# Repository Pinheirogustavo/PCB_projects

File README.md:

# PCB Projects

## Conexões presentes nas barras de pinos

### Barra de "tensoes"

- Earth: Terra virtual implementado com LM675
- VCC: +(MaxTensao da fonte utilizada / 2) Tensao NÃO regulada
- VEE:-(MaxTensao da fonte utilizada / 2)  Tensao NÃO regulada
- +9V: regulador 7809
- -9V: regulador 7909
- +5V: regulador 7805
- -5V: regulador 7905
- +3.3V: regulador 1117T-3.3

### Barra "Sinais analogicos"
- I1: corrente 1 dada pela fonte Howland
- I2: corrente 2 dada pela fonte Howland (caso bipolar)
- Ampl1: Tensão de saída condicionada do INA que monitora a corrente I1
- Ampl2: Tensão de saída condicionada do INA que monitora a corrente I2
- Sin1: Sinal alternado 1 gerado por AD9833/9850. Sem amplificação
- Sin2: Sinal alternado 2 gerado por AD9833/9850. Sem amplificação
- SinA: Sinal alternado 1 com controle de amplitude (talvez freq e fase)
- SinB: Sinal alternado 2 com controle de amplitude (talvez freq e fase)

### Barra "comunicacao"
- SINC: Sinal de sincronismo (ainda a definir)
- SDA(1-3)/SCL(1-3): Três pares de pinos reservados para comunicação - I2C
- SPI_COPI: comunicação SPI Controller Out Peripheral In
- SPI_CIPO: comunicação SPI Controller In, Peripheral Out
- SPI_clk: pino de clock que estabelece o sincronismo da comunicação SPI
- CS(x): pinos para selecionar o chip desejado (Chip Select)
> CS (AD9833): seleciona o gerador de sinais AD9833

> CS (X9c10x): seleciona o potenciometro digital do circuito de controle da corrente

###### comunicação I2C

SDA1/SCL1: implementado nos módulos "Gerador de sinais", com resistores pullup (Rp) para dispositivos de 3.3V;

SDA2/SCL2: implementado nos módulos "Fonte de corrente", com resistores pullup (Rp) para dispositivos de 5.0V. 

I2C arduino: https://docs.arduino.cc/learn/communication/wire

SPI arduino https://docs.arduino.cc/learn/communication/spi?_gl=1*1

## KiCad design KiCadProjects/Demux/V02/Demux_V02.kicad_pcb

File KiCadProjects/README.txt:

Versao do CAD: KiCad 7.0

------------------------------------------------------------------------------------------------------------------------------------------
Como adicionar bibliotecas

- Bibliotecas prontas da internet (salvar em Projeto Global): https://forum.digikey.com/t/importing-the-digi-key-kicad-library-into-kicad-5-0-0/4075
	caminho:/PCB_projects/KiCadProjects/libraries/

- Bibliotecas criadas pelo autor:  Usar o editor de simbolos e de footprint do kicad, salvar em Projeto Global
	caminho:/PCB_projects/KiCadProjects/libraries/MyCreates
------------------------------------------------------------------------------------------------------------------------------------------

Placa 90x100mm face simples

Trilhas azuis: trilhas dispostas na face de cobre inferior

Trilhas vermelhas: Representam jumpers, estao dispostas na face de cobre superior

------------------------------------------------------------------------------------------------------------------------------------------

Regras de layout PCB

- largura da trilha = 50 mils (1,27 mm)
 	O valor mínimo é de 8 mils, mas isso gera uma trilha extremamente fina
- Espaçamento entre trilhas = 50 mils (1,27 mm)
	O grid deve ser maior que o diâmetro da fresa utilizada (>0,2mm)
- Definir o algoritmo de auto-roteamento no CAD como “Grid Router” (precisa adicionar plugin)
- Definir o diâmetro do contorno em 0,5mm

------------------------------------------------------------------------------------------------------------------------------------------

Orientações para layout PCB

- Criar trilhas de alimentação, de terra e de clock.
- Fazer as trilhas de alimentação com largura maior
- Evitar trilhas muito longas
- Preferir mudanças de direção de 45º nas trilhas
- Evitar que trilhas de sinais críticos (clock e altas freqüências) fiquem paralelas por muito tempo
- Evitar ligações diretas entre as entradas de alimentação de Cis
- Colocar um LED indicando que a placa está energizada
-Colocar pontos de acesso para medir com o osciloscópio
- Usar soquetes para os CIs

------------------------------------------------------------------------------------------------------------------------------------------
Alguns footprints de componentes comuns e suas melhores  escolhas (ou até achar algo melhor)

Resistores -  11779 Resistor_THT:R_Axial_DIN0207_L6.3mm_D2.5mm_P7.62mm_Horizontal
Capacitores eletrolíticos - 525 Capacitor_THT:CP_Radial_D5.0mm_P2.50mm
Diodos -  7485 Diode_THT:D_DO-41_SOD81_P10.16mm_Horizontal
LED - 8642 LED_THT:LED_D5.0mm
conectores fêmea -  5813/6090 Connector_PinSocket_2.54mm:PinSocket_1xXX_P2.54mm_Vertical
conectores macho -  4855/5132 Connector_PinHeader_2.54mm:PinHeader_1xXX_P2.54mm_Vertical 
conector p4 de bateria - 1150 Connector_BarrelJack:BarrelJack_GCT_DCJ200-10-A_Horizontal

------------------------------------------------------------------------------------------------------------------------------------------
Tamanho de pad de componentes comuns e suas melhores  escolhas (ou até achar algo melhor). O tamanho do furo (0,8mm) não precisa ser configurado agora pois pode ser modificado na hora da produção (FlatCAM).

Resistores -  circular 2,5mm 
Capacitores eletrolíticos -  	+ circular 2mm	-retangular2x2,5mm
Diodos -   circular 2,5mm 
LED - 	+ circular 2mm	-retangular2x2,5mm
Barra de pinos - circular 2mm
conector p4 de bateria - oval3x4,2mm retangular4,6x3mm

------------------------------------------------------------------------------------------------------------------------------------------
FONTE DE TENSAO

v01;v02 SW1: Botão DPDT com trava para ligar e desligar a fonte. https://www.multcomercial.com.br/chave-push-button-7x7-com-trava.html
v03;v04 Chave gangorra kcd1 para ligar e desligar a fonte.

Os reguladores estao localizados na borda da placa, alinhados e igualmente espaçados, sendo possivel utilizar único dissipador

Segundo icone, ao lado do simbolo de disquete. Para editar as regras de furos, tamanhos de trilhas... sempre conferir. 

Icone de lista. Verifica as regras.

------------------------------------------------------------------------------------------------------------------------------------------

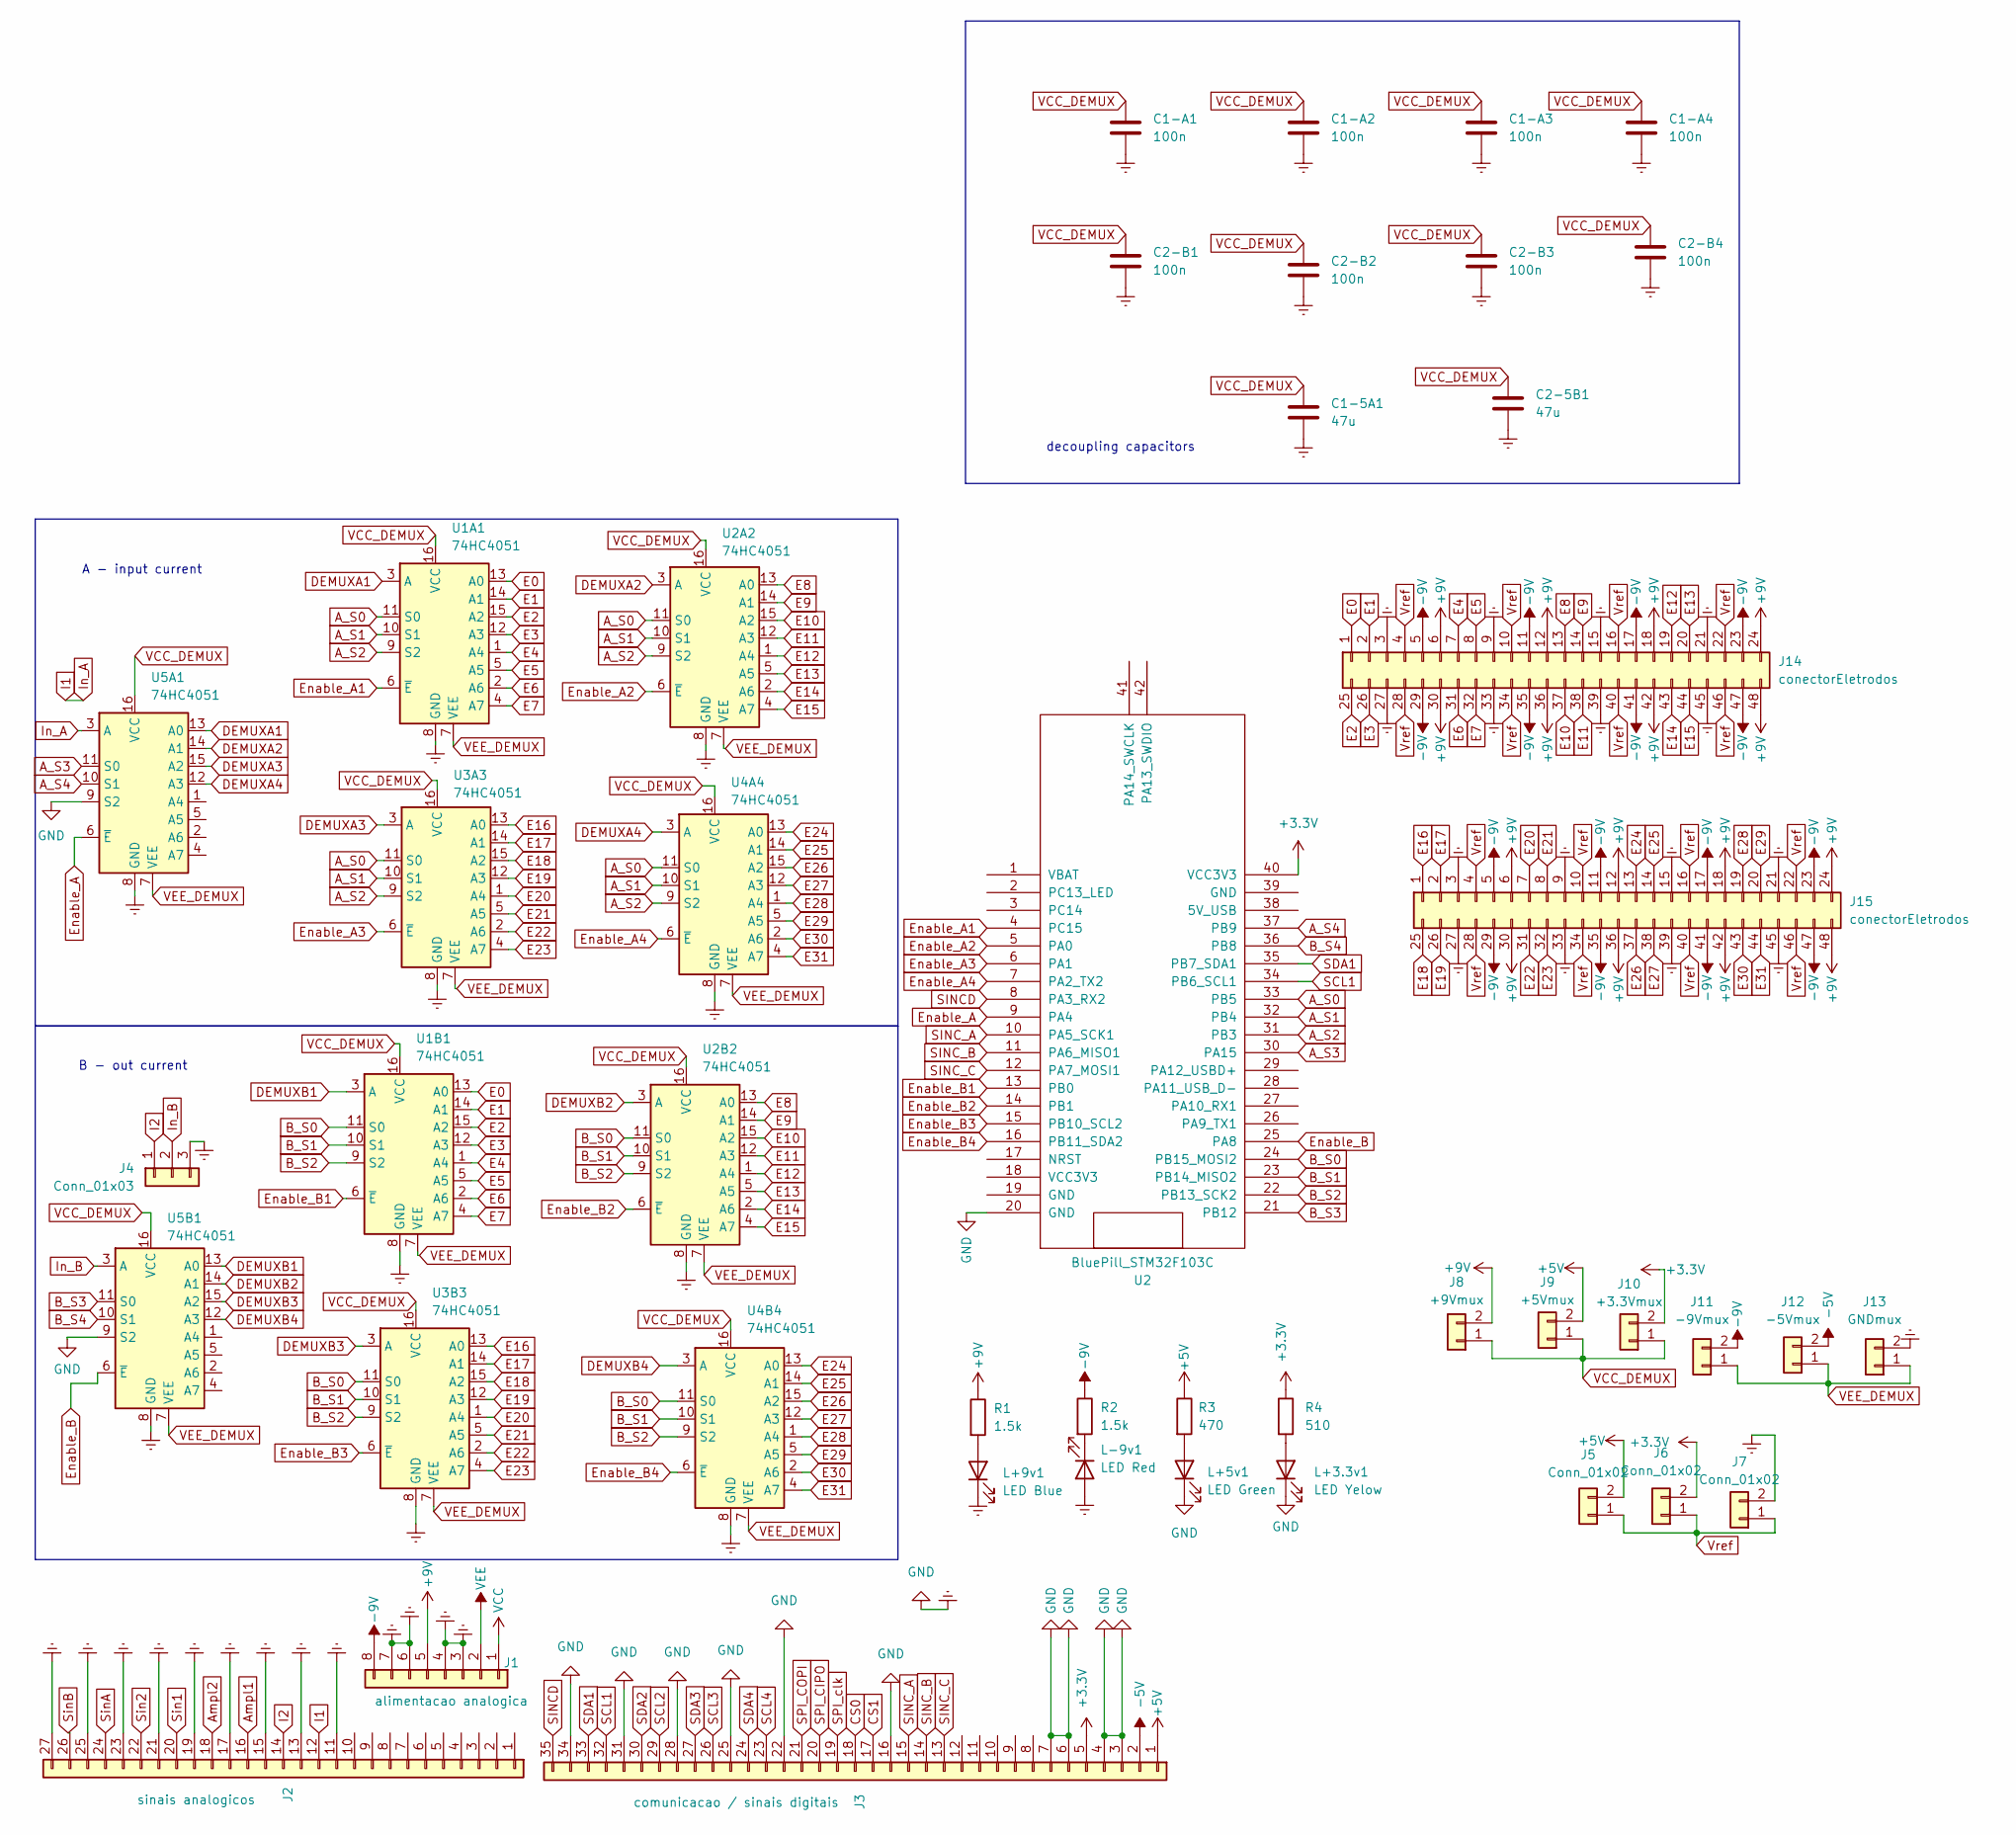
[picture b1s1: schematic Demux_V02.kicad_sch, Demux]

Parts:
C1-5A1, C2-5B1: 47u; CP_Radial_D5.0mm_P2.50mm
C1-A1, C1-A2, C1-A3, C1-A4, C2-B1, C2-B2, C2-B3, C2-B4: 100n; C_Disc_D3.0mm_W1.6mm_P2.50mm
J1: alimentacao analogica; PinHeader_1x08_P2.54mm_Vertical
J2: sinais analogicos; PinHeader_1x27_P2.54mm_Vertical
J3: comunicacao / sinais digitais; PinHeader_1x35_P2.54mm_Vertical
J4: Conn_01x03; PinHeader_1x03_P2.54mm_Vertical
J5, J6, J7: Conn_01x02; PinHeader_1x02_P2.54mm_Vertical
J8: +9Vmux; PinHeader_1x02_P2.54mm_Vertical
J9: +5Vmux; PinHeader_1x02_P2.54mm_Vertical
J10: +3.3Vmux; PinHeader_1x02_P2.54mm_Vertical
J11: -9Vmux; PinHeader_1x02_P2.54mm_Vertical
J12: -5Vmux; PinHeader_1x02_P2.54mm_Vertical
J13: GNDmux; PinHeader_1x02_P2.54mm_Vertical
J14, J15: conectorEletrodos; PinHeader_2x24_P2.54mm_Vertical
L+3.3v1: LED Yelow; LED_D5.0mm
L+5v1: LED Green; LED_D5.0mm
L+9v1: LED Blue; LED_D5.0mm
L-9v1: LED Red; LED_D5.0mm
R1, R2: 1.5k; R_Axial_DIN0207_L6.3mm_D2.5mm_P7.62mm_Horizontal
R3: 470; R_Axial_DIN0207_L6.3mm_D2.5mm_P7.62mm_Horizontal
R4: 510; R_Axial_DIN0207_L6.3mm_D2.5mm_P7.62mm_Horizontal
U1A1, U1B1, U2A2, U2B2, U3A3, U3B3, U4A4, U4B4, U5A1, U5B1: 74HC4051; N16
U2: BluePill_STM32F103C

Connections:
+3.3V: J3.5, J6.2, J10.2, R4.1, U2.40 (VCC3V3)
+5V: J3.1, J5.2, J9.2, R3.1
+9V: J1.5, J8.2, J14.6, J14.12, J14.18, J14.24, J14.30, J14.36, J14.42, J14.48, J15.6, J15.12, J15.18, J15.24, J15.30, J15.36, J15.42, J15.48, R1.1
-5V: J3.2, J12.2
-9V: J1.8, J11.2, J14.5, J14.11, J14.17, J14.23, J14.29, J14.35, J14.41, J14.47, J15.5, J15.11, J15.17, J15.23, J15.29, J15.35, J15.41, J15.47, R2.1
A_S0: U1A1.11 (S0), U2.33 (PB5), U2A2.11 (S0), U3A3.11 (S0), U4A4.11 (S0)
A_S1: U1A1.10 (S1), U2.32 (PB4), U2A2.10 (S1), U3A3.10 (S1), U4A4.10 (S1)
A_S2: U1A1.9 (S2), U2.31 (PB3), U2A2.9 (S2), U3A3.9 (S2), U4A4.9 (S2)
A_S3: U2.30 (PA15), U5A1.11 (S0)
A_S4: U2.37 (PB9), U5A1.10 (S1)
Ampl1: J2.16
Ampl2: J2.18
B_S0: U1B1.11 (S0), U2.24 (PB15_MOSI2), U2B2.11 (S0), U3B3.11 (S0), U4B4.11 (S0)
B_S1: U1B1.10 (S1), U2.23 (PB14_MISO2), U2B2.10 (S1), U3B3.10 (S1), U4B4.10 (S1)
B_S2: U1B1.9 (S2), U2.22 (PB13_SCK2), U2B2.9 (S2), U3B3.9 (S2), U4B4.9 (S2)
B_S3: U2.21 (PB12), U5B1.11 (S0)
B_S4: U2.36 (PB8), U5B1.10 (S1)
CS0: J3.18
CS1: J3.17
DEMUXA1: U1A1.3 (A), U5A1.13 (A0)
DEMUXA2: U2A2.3 (A), U5A1.14 (A1)
DEMUXA3: U3A3.3 (A), U5A1.15 (A2)
DEMUXA4: U4A4.3 (A), U5A1.12 (A3)
DEMUXB1: U1B1.3 (A), U5B1.13 (A0)
DEMUXB2: U2B2.3 (A), U5B1.14 (A1)
DEMUXB3: U3B3.3 (A), U5B1.15 (A2)
DEMUXB4: U4B4.3 (A), U5B1.12 (A3)
E0: J14.1, U1A1.13 (A0), U1B1.13 (A0)
E1: J14.2, U1A1.14 (A1), U1B1.14 (A1)
E2: J14.25, U1A1.15 (A2), U1B1.15 (A2)
E3: J14.26, U1A1.12 (A3), U1B1.12 (A3)
E4: J14.7, U1A1.1 (A4), U1B1.1 (A4)
E5: J14.8, U1A1.5 (A5), U1B1.5 (A5)
E6: J14.31, U1A1.2 (A6), U1B1.2 (A6)
E7: J14.32, U1A1.4 (A7), U1B1.4 (A7)
E8: J14.13, U2A2.13 (A0), U2B2.13 (A0)
E9: J14.14, U2A2.14 (A1), U2B2.14 (A1)
E10: J14.37, U2A2.15 (A2), U2B2.15 (A2)
E11: J14.38, U2A2.12 (A3), U2B2.12 (A3)
E12: J14.19, U2A2.1 (A4), U2B2.1 (A4)
E13: J14.20, U2A2.5 (A5), U2B2.5 (A5)
E14: J14.43, U2A2.2 (A6), U2B2.2 (A6)
E15: J14.44, U2A2.4 (A7), U2B2.4 (A7)
E16: J15.1, U3A3.13 (A0), U3B3.13 (A0)
E17: J15.2, U3A3.14 (A1), U3B3.14 (A1)
E18: J15.25, U3A3.15 (A2), U3B3.15 (A2)
E19: J15.26, U3A3.12 (A3), U3B3.12 (A3)
E20: J15.7, U3A3.1 (A4), U3B3.1 (A4)
E21: J15.8, U3A3.5 (A5), U3B3.5 (A5)
E22: J15.31, U3A3.2 (A6), U3B3.2 (A6)
E23: J15.32, U3A3.4 (A7), U3B3.4 (A7)
E24: J15.13, U4A4.13 (A0), U4B4.13 (A0)
E25: J15.14, U4A4.14 (A1), U4B4.14 (A1)
E26: J15.37, U4A4.15 (A2), U4B4.15 (A2)
E27: J15.38, U4A4.12 (A3), U4B4.12 (A3)
E28: J15.19, U4A4.1 (A4), U4B4.1 (A4)
E29: J15.20, U4A4.5 (A5), U4B4.5 (A5)
E30: J15.43, U4A4.2 (A6), U4B4.2 (A6)
E31: J15.44, U4A4.4 (A7), U4B4.4 (A7)
Earth: C1-5A1.2, C1-A1.2, C1-A2.2, C1-A3.2, C1-A4.2, C2-5B1.2, C2-B1.2, C2-B2.2, C2-B3.2, C2-B4.2, J1.3, J1.4, J1.6, J1.7, J2.11, J2.13, J2.15, J2.17, J2.19, J2.21, J2.23, J2.25, J2.27, J3.3, J3.4, J3.6, J3.7, J3.16, J3.22, J3.25, J3.28, J3.31, J3.34, J4.3, J7.2, J13.2, J14.3, J14.9, J14.15, J14.21, J14.27, J14.33, J14.39, J14.45, J15.3, J15.9, J15.15, J15.21, J15.27, J15.33, J15.39, J15.45, L+3.3v1.1 (K), L+5v1.1 (K), L+9v1.1 (K), L-9v1.2 (A), U1A1.8 (GND), U1B1.8 (GND), U2.20 (GND), U2A2.8 (GND), U2B2.8 (GND), U3A3.8 (GND), U3B3.8 (GND), U4A4.8 (GND), U4B4.8 (GND), U5A1.8 (GND), U5A1.9 (S2), U5B1.8 (GND), U5B1.9 (S2)
Enable_A: U2.9 (PA4), U5A1.6 (~E)
Enable_A1: U1A1.6 (~E), U2.4 (PC15)
Enable_A2: U2.5 (PA0), U2A2.6 (~E)
Enable_A3: U2.6 (PA1), U3A3.6 (~E)
Enable_A4: U2.7 (PA2_TX2), U4A4.6 (~E)
Enable_B: U2.25 (PA8), U5B1.6 (~E)
Enable_B1: U1B1.6 (~E), U2.13 (PB0)
Enable_B2: U2.14 (PB1), U2B2.6 (~E)
Enable_B3: U2.15 (PB10_SCL2), U3B3.6 (~E)
Enable_B4: U2.16 (PB11_SDA2), U4B4.6 (~E)
I1: J2.12, U5A1.3 (A)
I2: J2.14, J4.1
In_B: J4.2, U5B1.3 (A)
unnamed: L+3.3v1.2 (A), R4.2
unnamed: L+5v1.2 (A), R3.2
unnamed: L+9v1.2 (A), R1.2
unnamed: L-9v1.1 (K), R2.2
SCL1: J3.32, U2.34 (PB6_SCL1)
SCL2: J3.29
SCL3: J3.26
SCL4: J3.23
SDA1: J3.33, U2.35 (PB7_SDA1)
SDA2: J3.30
SDA3: J3.27
SDA4: J3.24
SINCD: J3.35, U2.8 (PA3_RX2)
SINC_A: J3.15, U2.10 (PA5_SCK1)
SINC_B: J3.14, U2.11 (PA6_MISO1)
SINC_C: J3.13, U2.12 (PA7_MOSI1)
SPI_CIPO: J3.20
SPI_COPI: J3.21
SPI_clk: J3.19
Sin1: J2.20
Sin2: J2.22
SinA: J2.24
SinB: J2.26
VCC: J1.1
VCC_DEMUX: C1-5A1.1, C1-A1.1, C1-A2.1, C1-A3.1, C1-A4.1, C2-5B1.1, C2-B1.1, C2-B2.1, C2-B3.1, C2-B4.1, J8.1, J9.1, J10.1, U1A1.16 (VCC), U1B1.16 (VCC), U2A2.16 (VCC), U2B2.16 (VCC), U3A3.16 (VCC), U3B3.16 (VCC), U4A4.16 (VCC), U4B4.16 (VCC), U5A1.16 (VCC), U5B1.16 (VCC)
VEE: J1.2
VEE_DEMUX: J11.1, J12.1, J13.1, U1A1.7 (VEE), U1B1.7 (VEE), U2A2.7 (VEE), U2B2.7 (VEE), U3A3.7 (VEE), U3B3.7 (VEE), U4A4.7 (VEE), U4B4.7 (VEE), U5A1.7 (VEE), U5B1.7 (VEE)
Vref: J5.1, J6.1, J7.1, J14.4, J14.10, J14.16, J14.22, J14.28, J14.34, J14.40, J14.46, J15.4, J15.10, J15.16, J15.22, J15.28, J15.34, J15.40, J15.46

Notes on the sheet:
decoupling capacitors
A - input current
B - out current

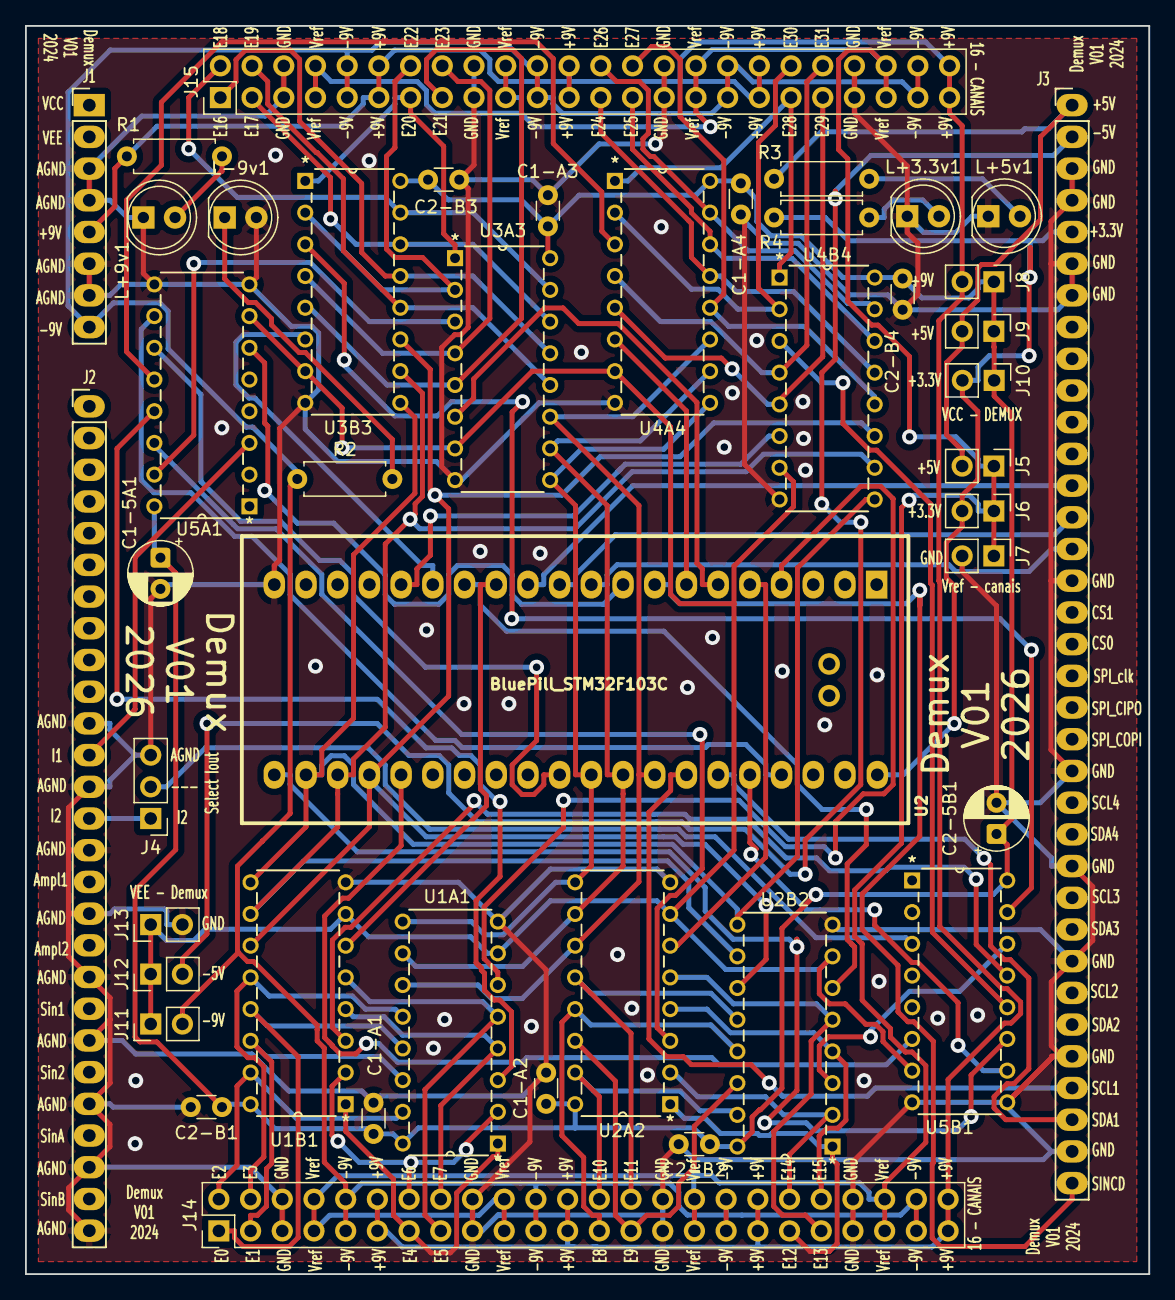
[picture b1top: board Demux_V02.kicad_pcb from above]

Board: 2 copper layers, 90.0 x 100.0 mm, 44 parts (0 on the bottom side), 82 nets.

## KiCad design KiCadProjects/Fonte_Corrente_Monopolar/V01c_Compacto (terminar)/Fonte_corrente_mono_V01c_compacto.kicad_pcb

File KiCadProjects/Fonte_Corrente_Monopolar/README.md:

# Fonte de corrente monopolar

## Versão atualmente implementada no tomógrafo: V02

## Descrição Geral do projeto

Fonte de corrente controlada por tensão monopolar do tipo Howoland aperfeiçoada. O Sistema é excitado por um sinal senoidal e fornece uma corrente alternada de amplitude constante frente uma banda de resistências. Há um sistema de monitoramento da amplitude da corrente (Ampl1) que é implementado com um circuito de condicionamento dedicado.

Estágios Fonte de Corrente: Sinal de entrada(Sin1 ou SinA) &rarr; buffer &rarr; arquitetura fonte Howland &rarr; Resistor Sentinela//Amplificador de Instrumentação &rarr;  corrente I1.

Estágios monitoramento: Amplificador de Instrumentação &rarr; AmpOp &rarr; circuito de condicionamento &rarr; amplitude da corrente Ampl1.

## Componentes do circuito:

- Amplificador Operacional Dual AD826/828: Amplificador operacional duplo implementado como buffer na entrada do sistema e de acordo com a arquitetura da fonte Howland aperfeiçoada.
	>Amplificador 1: buffer.
	
	>Amplificador 2: arquitetura da fonte Howland aperfeiçoada.
- Resistor sentinela: Resistor de baixa resistência em série com a saída da fonte Howland. Implementado para monitorar a corrente gerada.
- Amplificador de Instrumentação INA: Amplificador de Instrumentação verifica a tensão sobre o resistor sentinela e aplica alto ganho fixo. A tensão de saída é condicionada e indica a amplitude da corrente (Ampl1).  Implementado para monitorar a corrente gerada. 
- Circuito de condicionamento: Condiciona o sinal para os limites do ADC do controlador (Selecionado com jumpers nos pinos "Vref" 3.3/5V). 

## Cuidados a serem tomados

## Estágios do circuito

#### Entrada do sinal de controle de corrente:

O sinal de entrada (Vin) determina a amplitude e frequência da corrente gerada. O sistema permite dois sinais de entrada, Sin1 e SinA, que são selecionados por uma chave gangorra kcd1.

A frequência da corrente é a mesma do sinal de entrada Vin. A amplitude da corrente é dada por:

$$ I = \frac{V_{in}}{R_6} $$

#### Buffer:

Buffer implementado na entrada do sistema com o amplificador operacional dual uma vez que o circuito do gerador de sinais foi projetado sem buffer em sua saída.

#### Arquitetura fonte Howland:

Fonte monopolar do tipo Howland aperfeiçoada.

#### Resistor sentinela e amplificador de instrumentação

#### Circuito de condicionamento

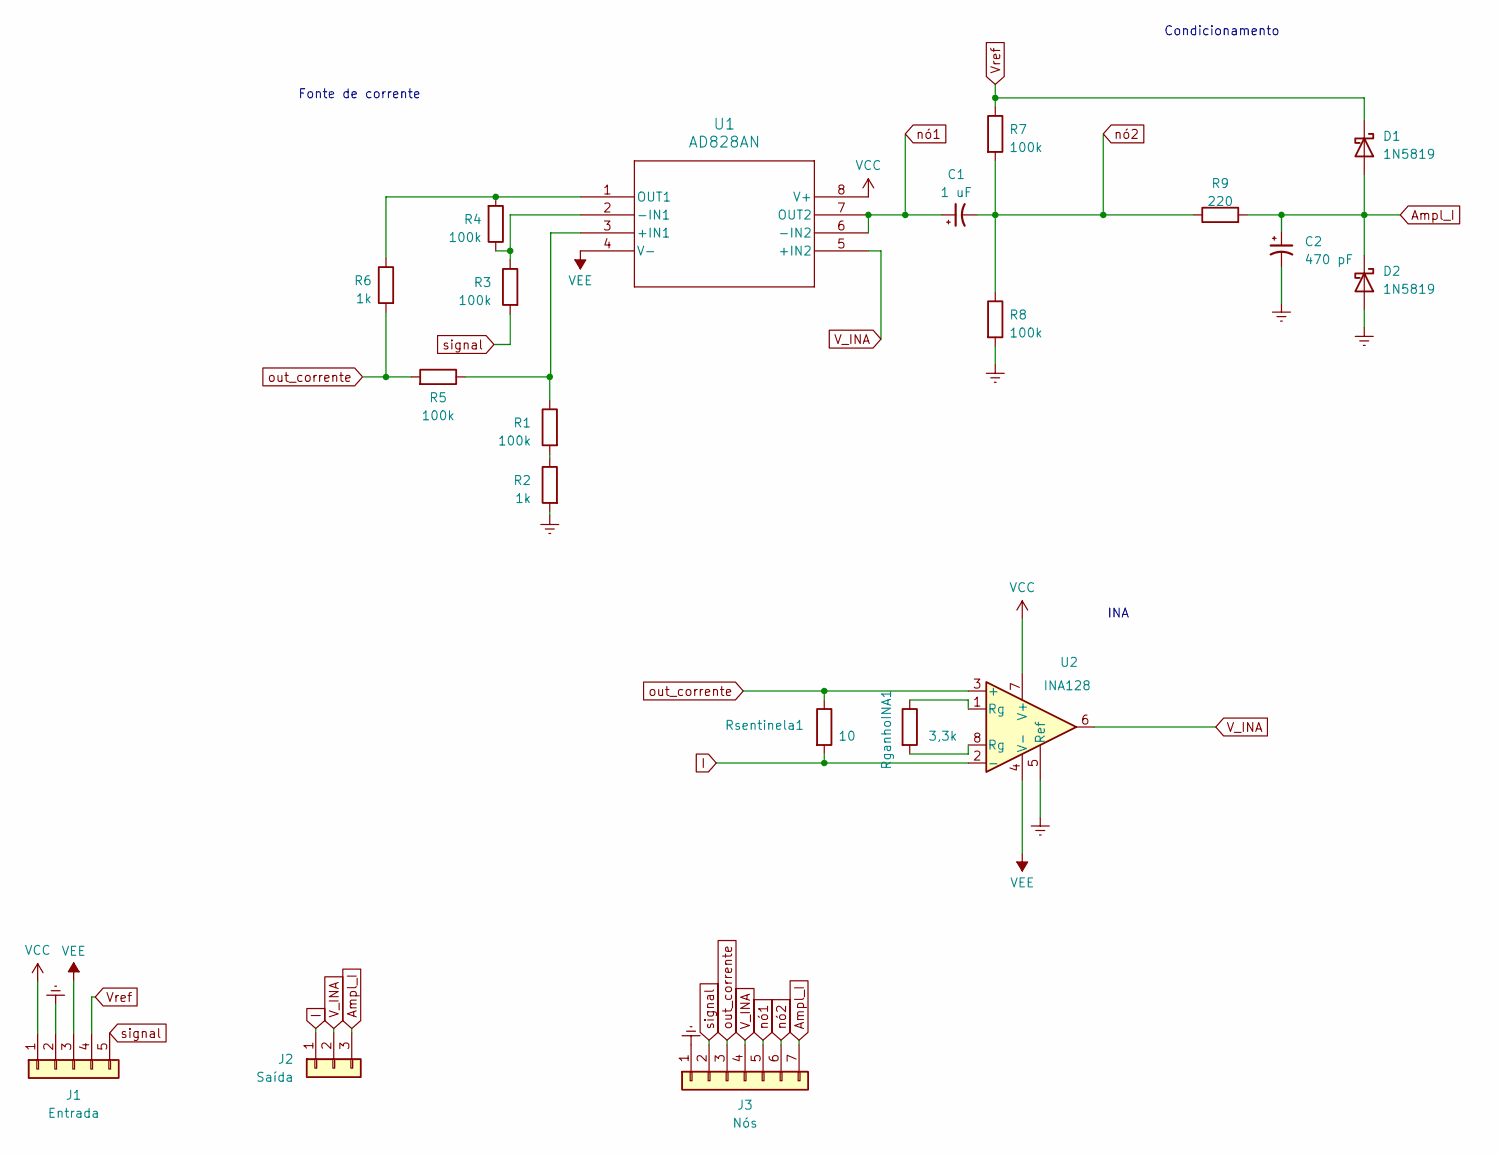
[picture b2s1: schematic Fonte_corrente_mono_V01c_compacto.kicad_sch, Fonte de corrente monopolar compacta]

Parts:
C1: 1 uF; CP_Radial_D5.0mm_P2.50mm
C2: 470 pF; CP_Radial_D5.0mm_P2.50mm
D1, D2: 1N5819; D_DO-41_SOD81_P10.16mm_Horizontal
J1: Entrada; PinSocket_1x05_P2.54mm_Vertical
J2: Saída; PinSocket_1x03_P2.54mm_Vertical
J3: Nós; PinHeader_1x07_P2.54mm_Vertical
R1, R3, R4, R5, R7, R8: 100k; R_Axial_DIN0207_L6.3mm_D2.5mm_P7.62mm_Horizontal
R2, R6: 1k; R_Axial_DIN0207_L6.3mm_D2.5mm_P7.62mm_Horizontal
R9: 220; R_Axial_DIN0207_L6.3mm_D2.5mm_P7.62mm_Horizontal
RganhoINA1: 3,3k; R_Axial_DIN0207_L6.3mm_D2.5mm_P7.62mm_Horizontal
Rsentinela1: 10; R_Axial_DIN0207_L6.3mm_D2.5mm_P7.62mm_Horizontal
U1: AD828AN; N_8_ADI
U2: INA128; DIP-8_W7.62mm

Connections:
Ampl_I: C2.1, D1.2 (A), D2.1 (K), J2.3, J3.7, R9.2
Earth: C2.2, D2.2 (A), J1.2, J3.1, R2.2, R8.2, U2.5 (Ref)
I: J2.1, Rsentinela1.2, U2.2 (-)
unnamed: R1.2, R2.1
unnamed: RganhoINA1.1, U2.1 (Rg)
unnamed: RganhoINA1.2, U2.8 (Rg)
unnamed: R1.1, R5.1, U1.3 (+IN1)
unnamed: R3.1, R4.1, U1.2 (-IN1)
unnamed: R4.2, R6.1, U1.1 (OUT1)
VCC: J1.1, U1.8 (V+), U2.7 (V+)
VEE: J1.3, U1.4 (V-), U2.4 (V-)
V_INA: J2.2, J3.4, U1.5 (+IN2), U2.6
Vref: D1.1 (K), J1.4, R7.1
nó1: C1.1, J3.5, U1.6 (-IN2), U1.7 (OUT2)
nó2: C1.2, J3.6, R7.2, R8.1, R9.1
out_corrente: J3.3, R5.2, R6.2, Rsentinela1.1, U2.3 (+)
signal: J1.5, J3.2, R3.2

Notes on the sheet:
Condicionamento
Fonte de corrente
INA

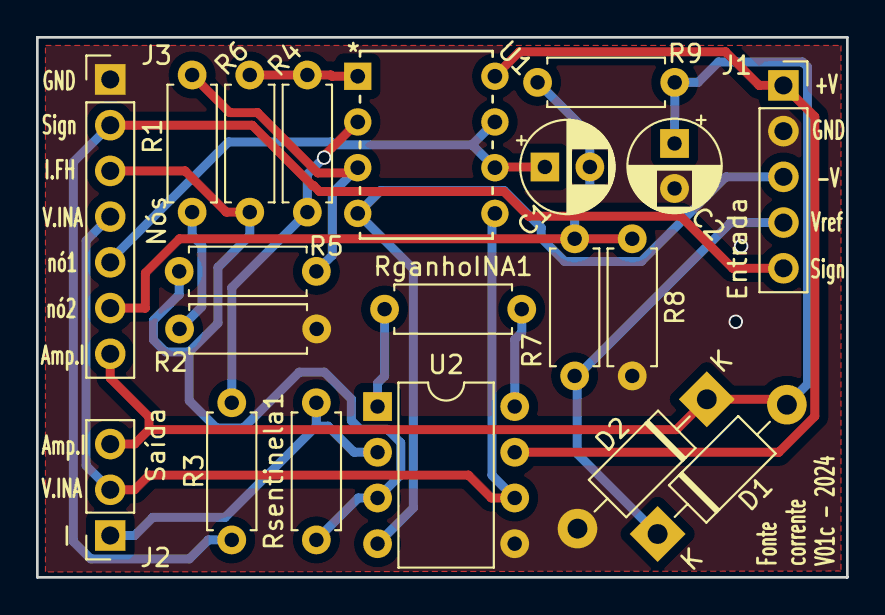
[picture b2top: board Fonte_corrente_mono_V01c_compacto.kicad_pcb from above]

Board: 2 copper layers, 45.0 x 30.0 mm, 20 parts (0 on the bottom side), 17 nets.

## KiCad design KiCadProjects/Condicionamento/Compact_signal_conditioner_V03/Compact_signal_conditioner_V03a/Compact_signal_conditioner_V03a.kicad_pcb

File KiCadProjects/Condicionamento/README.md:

# Placa de condicionamento de sinal

## Versões em produção (jlcpcb):condicionamento_compacto_V01a; condicionamento_compacto_V01b; condicionamento_Aquisicao_BIA_v03

## Descrição Geral do projeto

Circuito de condicionamento de sinal para aquisição por microcontrolador.

# Versões do projeto:

## condicionamento_compacto_V01

Circuito projetado para apenas condicionar o sinal de interesse para correta aquisição do microcontrolador utilizado, buscando não alterar nenhuma característica do sinal.

Estágios: Sinais a serem condicionados &rarr; buffer &rarr; offset (valor médio do limite de entrada do ADC) &rarr; diodos de proteção ( limites de entrada do ADC) &rarr; Filtro anti-aliasing &rarr; sinal condicionado &rarr; ADC@uC

O circuito de condicionamento permite a adequada aquisição de sinal por meio de microcontrolador, garantindo que os sinais aplicados nas entradas do dispositivo não ultrapassem os limites de tensão e corrente suportados, além da adequada amostragem do sinal, por meio de filtro anti-aliasing. Esse circuito emprega o amplificador operacional dual, o que permite o condicionamento de dois canais. Os estágios do circuito são:

- buffer: amplificador operacional no modo seguidor, configuração de alta impedância de entrada que permite o adequado acoplamento entre os estágios do sistema, minimizando a interação entre eles.

- Offset: estágio que realiza um deslocamento (offset) do sinal de entrada, adequando os sinais alternados de correntes do circuito aos ADCs do microcontrolador, adicionando um sinal DC equivalente ao valor médio do limite de entrada dos ADCS. O valor de Vref pode ser escolhido por um pino de entrada do circuito.

- Diodos de proteção: não permitem que o sinal de entrada ultrapasse  os limites de entrada do conversor ADC.

- filtro anti-alising: Frequência de corte $F_c$:

$$F_c = \frac{1}{2\cdot\pi\cdot R\cdot C} = \frac{1}{2\cdot\pi\cdot220\cdot470\cdot10 ^{-12}} = 1,5 MHz$$
**ALTERAR LEVANDO EM CONTA OS OUTROS COMPONENTES**

## condicionamento_compacto_V02

Circuito projeto para, além de condicionar o sinal de interesse para os limites de operação do microcontrolador, aplicar um ganho ao sinal de interesse em busca de melhorar a relação sinal-ruído obtida.

Estágios: Sinais a serem condicionados &rarr; buffer &rarr; amplificador não inversor com variação da resistência de entrada por controle eletrônico  &rarr; offset (valor médio do limite de entrada do ADC) &rarr; diodos de proteção ( limites de entrada do ADC) &rarr; Filtro anti-aliasing &rarr; sinal condicionado &rarr; ADC@uC

## condicionamento_Aquisicao_BIA_v01

Circuito projetado para condicionamento e aquisição de apenas 4 canais para um Analisador de Bioimpedância.

## condicionamento_Aquisicao_BIA_v02

Circuito projetado para condicionamento e aquisição de apenas 4 canais para um Analisador de Bioimpedância.

## condicionamento_Aquisicao_BIA_v03

Circuito projetado para condicionamento e aquisição de apenas 4 canais para um Analisador de Bioimpedância.

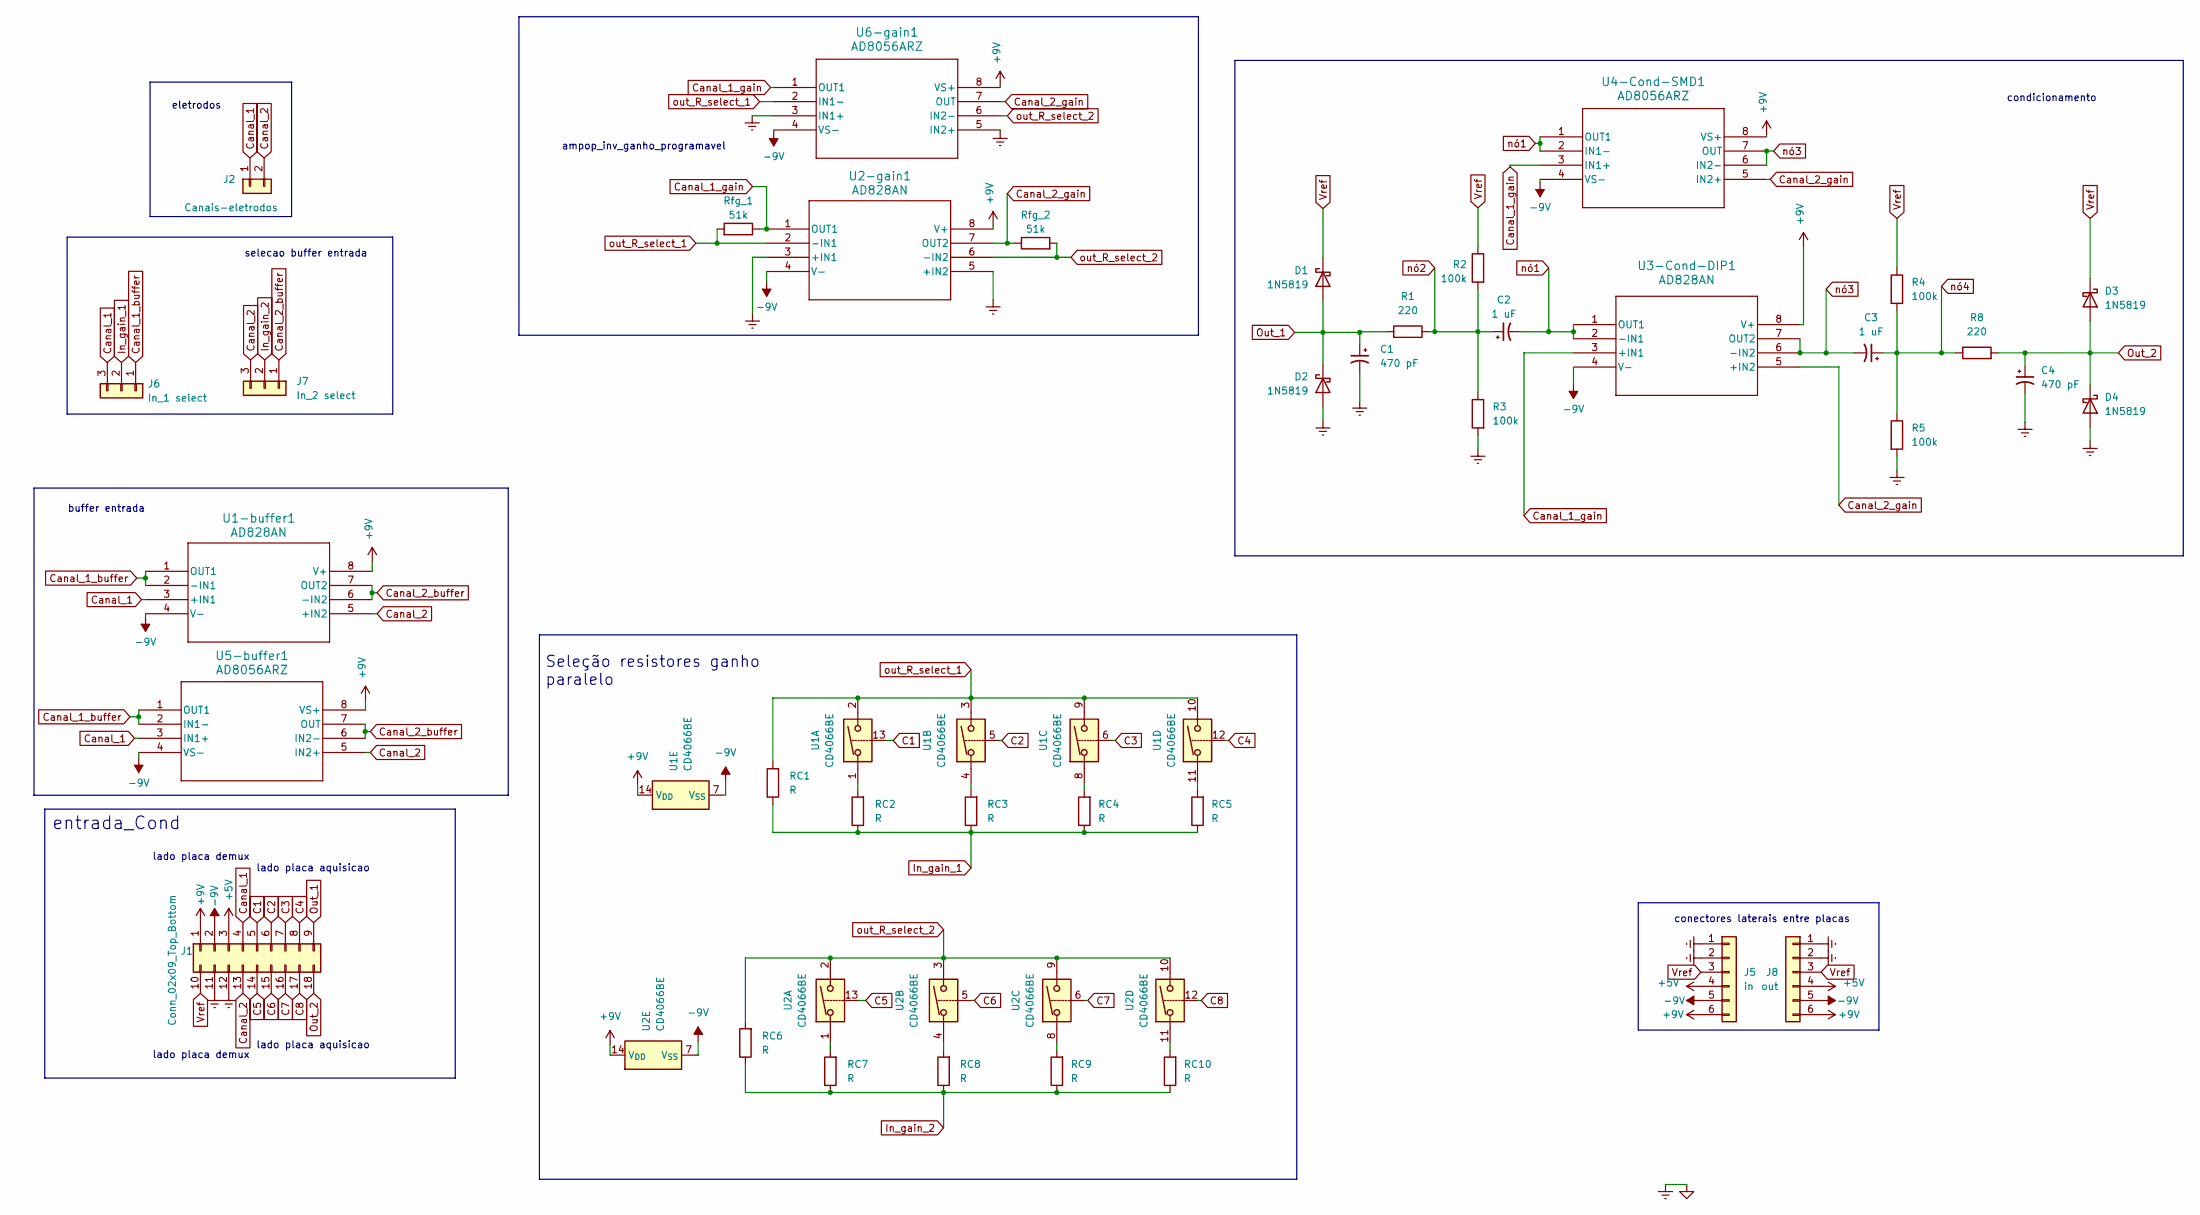
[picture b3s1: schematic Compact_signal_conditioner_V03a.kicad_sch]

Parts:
C1, C4: 470 pF; CP_Radial_D5.0mm_P2.50mm
C2, C3: 1 uF; CP_Radial_D5.0mm_P2.50mm
D1, D2, D3, D4: 1N5819; D_DO-41_SOD81_P10.16mm_Horizontal
J1: Conn_02x09_Top_Bottom; PinSocket_2x09_P2.54mm_Horizontal
J2: Canais-eletrodos; PinHeader_1x02_P2.54mm_Vertical
J5: in; PinSocket_1x06_P2.54mm_Horizontal
J6: In_1 select; PinHeader_1x03_P2.54mm_Vertical
J7: In_2 select; PinHeader_1x03_P2.54mm_Vertical
J8: out; PinHeader_1x06_P2.54mm_Horizontal
R1, R8: 220; R_Axial_DIN0207_L6.3mm_D2.5mm_P7.62mm_Horizontal
R2, R3, R4, R5: 100k; R_Axial_DIN0207_L6.3mm_D2.5mm_P7.62mm_Horizontal
RC1, RC2, RC3, RC4, RC5, RC6, RC7, RC8, RC9, RC10: R; R_Axial_DIN0207_L6.3mm_D2.5mm_P7.62mm_Horizontal
Rfg_1, Rfg_2: 51k; R_Axial_DIN0207_L6.3mm_D2.5mm_P7.62mm_Horizontal
U1, U2: CD4066BE; DIP-14_W7.62mm
U1-buffer1, U2-gain1, U3-Cond-DIP1: AD828AN; N_8_ADI
U4-Cond-SMD1, U5-buffer1, U6-gain1: AD8056ARZ; R_8_ADI

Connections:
+5V: J1.3, J5.4, J8.4
+9V: J1.1, J5.6, J8.6, U1.14 (V_{DD}), U1-buffer1.8 (V+), U2.14 (V_{DD}), U2-gain1.8 (V+), U3-Cond-DIP1.8 (V+), U4-Cond-SMD1.8 (VS+), U5-buffer1.8 (VS+), U6-gain1.8 (VS+)
-9V: J1.2, J5.5, J8.5, U1.7 (V_{SS}), U1-buffer1.4 (V-), U2.7 (V_{SS}), U2-gain1.4 (V-), U3-Cond-DIP1.4 (V-), U4-Cond-SMD1.4 (VS-), U5-buffer1.4 (VS-), U6-gain1.4 (VS-)
C1: J1.5, U1.13
C2: J1.6, U1.5
C3: J1.7, U1.6
C4: J1.8, U1.12
C5: J1.14, U2.13
C6: J1.15, U2.5
C7: J1.16, U2.6
C8: J1.17, U2.12
Canal_1: J1.4, J2.1, J6.3, U1-buffer1.3 (+IN1), U5-buffer1.3 (IN1+)
Canal_1_buffer: J6.1, U1-buffer1.1 (OUT1), U1-buffer1.2 (-IN1), U5-buffer1.1 (OUT1), U5-buffer1.2 (IN1-)
Canal_1_gain: Rfg_1.1, U2-gain1.1 (OUT1), U3-Cond-DIP1.3 (+IN1), U4-Cond-SMD1.3 (IN1+), U6-gain1.1 (OUT1)
Canal_2: J1.13, J2.2, J7.3, U1-buffer1.5 (+IN2), U5-buffer1.5 (IN2+)
Canal_2_buffer: J7.1, U1-buffer1.6 (-IN2), U1-buffer1.7 (OUT2), U5-buffer1.6 (IN2-), U5-buffer1.7 (OUT)
Canal_2_gain: Rfg_2.1, U2-gain1.7 (OUT2), U3-Cond-DIP1.5 (+IN2), U4-Cond-SMD1.5 (IN2+), U6-gain1.7 (OUT)
Earth: C1.2, C4.2, D2.2 (A), D4.2 (A), J1.11, J1.12, J5.1, J5.2, J8.1, J8.2, R3.2, R5.2, U2-gain1.3 (+IN1), U2-gain1.5 (+IN2), U6-gain1.3 (IN1+), U6-gain1.5 (IN2+)
In_gain_1: J6.2, RC1.1, RC2.1, RC3.1, RC4.1, RC5.1
In_gain_2: J7.2, RC6.1, RC7.1, RC8.1, RC9.1, RC10.1
unnamed: RC2.2, U1.1
unnamed: RC3.2, U1.4
unnamed: RC4.2, U1.8
unnamed: RC5.2, U1.11
unnamed: RC7.2, U2.1
unnamed: RC8.2, U2.4
unnamed: RC9.2, U2.8
unnamed: RC10.2, U2.11
Out_1: C1.1, D1.2 (A), D2.1 (K), J1.9, R1.2
Out_2: C4.1, D3.2 (A), D4.1 (K), J1.18, R8.2
Vref: D1.1 (K), D3.1 (K), J1.10, J5.3, J8.3, R2.1, R4.1
nó1: C2.2, U3-Cond-DIP1.1 (OUT1), U3-Cond-DIP1.2 (-IN1), U4-Cond-SMD1.1 (OUT1), U4-Cond-SMD1.2 (IN1-)
nó2: C2.1, R1.1, R2.2, R3.1
nó3: C3.2, U3-Cond-DIP1.6 (-IN2), U3-Cond-DIP1.7 (OUT2), U4-Cond-SMD1.6 (IN2-), U4-Cond-SMD1.7 (OUT)
nó4: C3.1, R4.2, R5.1, R8.1
out_R_select_1: RC1.2, Rfg_1.2, U1.2, U1.3, U1.9, U1.10, U2-gain1.2 (-IN1), U6-gain1.2 (IN1-)
out_R_select_2: RC6.2, Rfg_2.2, U2.2, U2.3, U2.9, U2.10, U2-gain1.6 (-IN2), U6-gain1.6 (IN2-)

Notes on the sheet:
selecao buffer entrada
eletrodos
lado placa demux
entrada_Cond
lado placa aquisicao
Seleção resistores ganho paralelo
condicionamento
conectores laterais entre placas
ampop_inv_ganho_programavel
buffer entrada

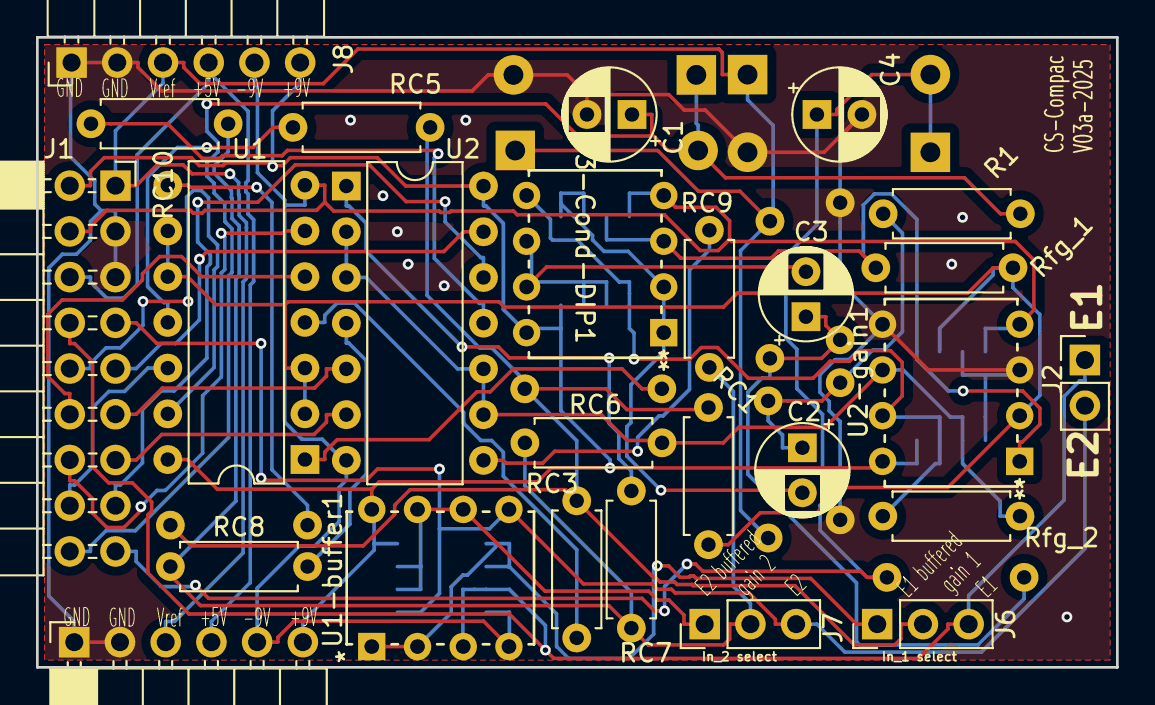
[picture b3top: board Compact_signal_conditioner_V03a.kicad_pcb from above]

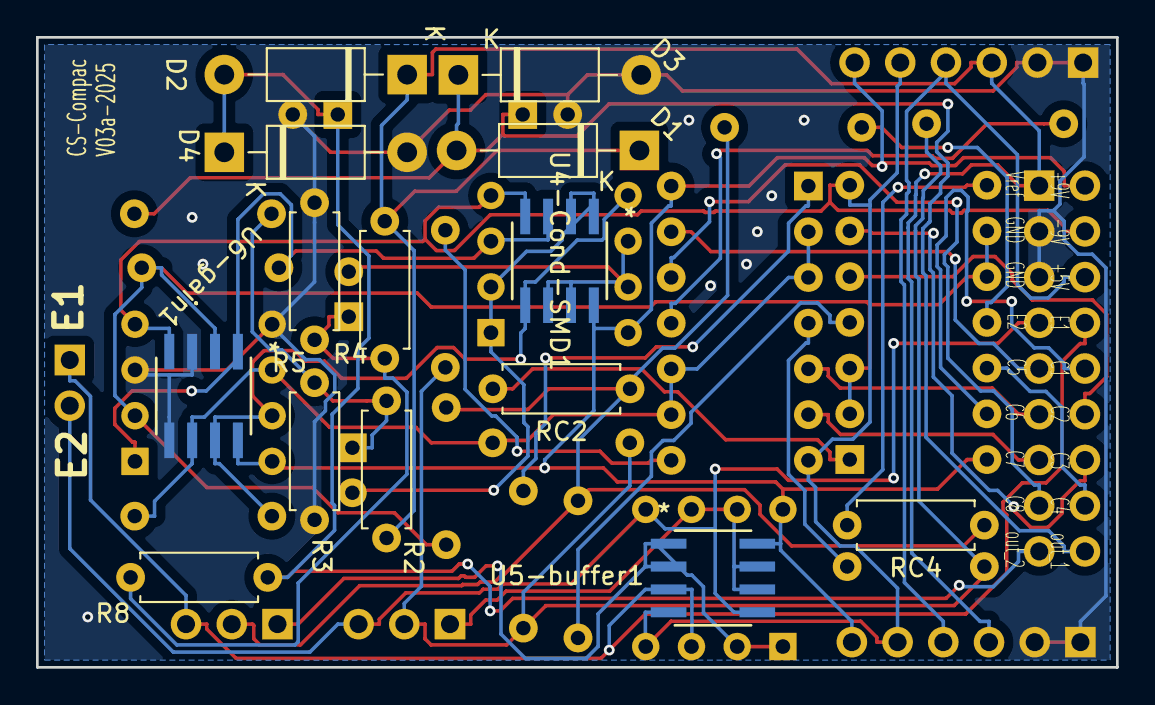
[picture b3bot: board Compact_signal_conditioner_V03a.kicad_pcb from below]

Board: 2 copper layers, 60.0 x 35.0 mm, 40 parts (14 on the bottom side), 37 nets.
